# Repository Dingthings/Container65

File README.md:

Simple Arduino Pro-micro based keyboard with QMK support

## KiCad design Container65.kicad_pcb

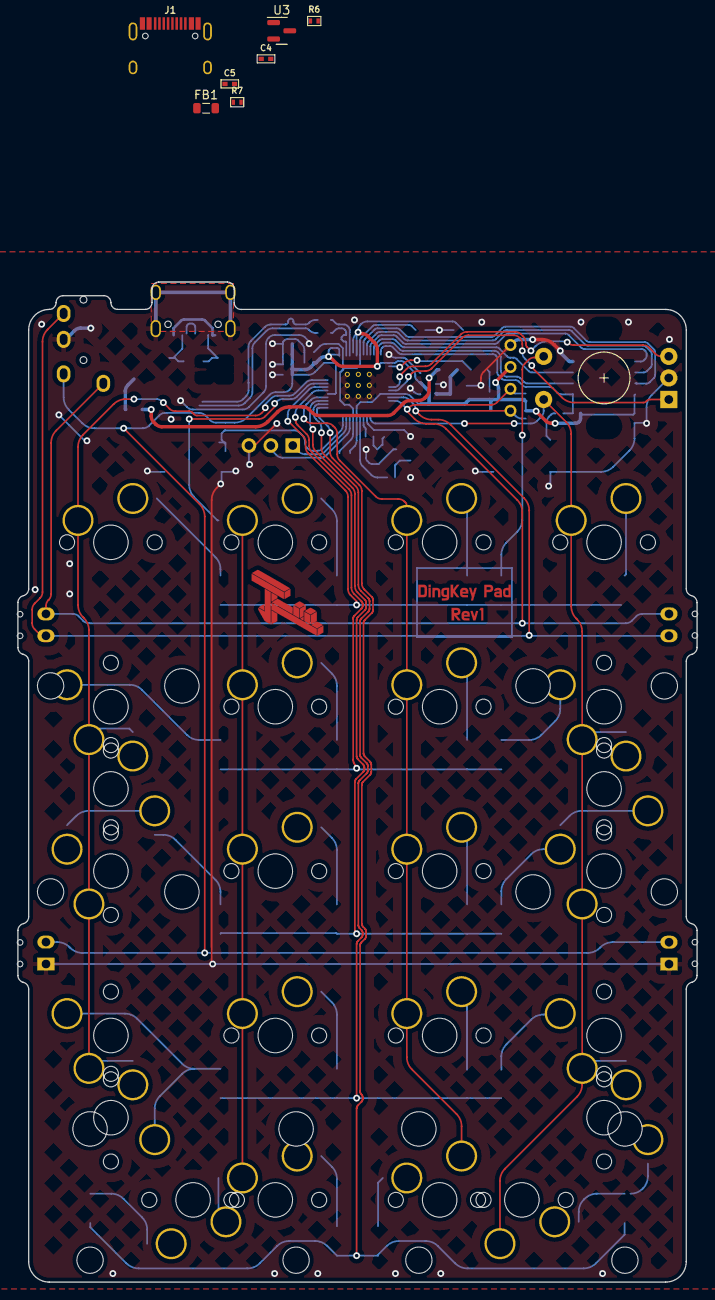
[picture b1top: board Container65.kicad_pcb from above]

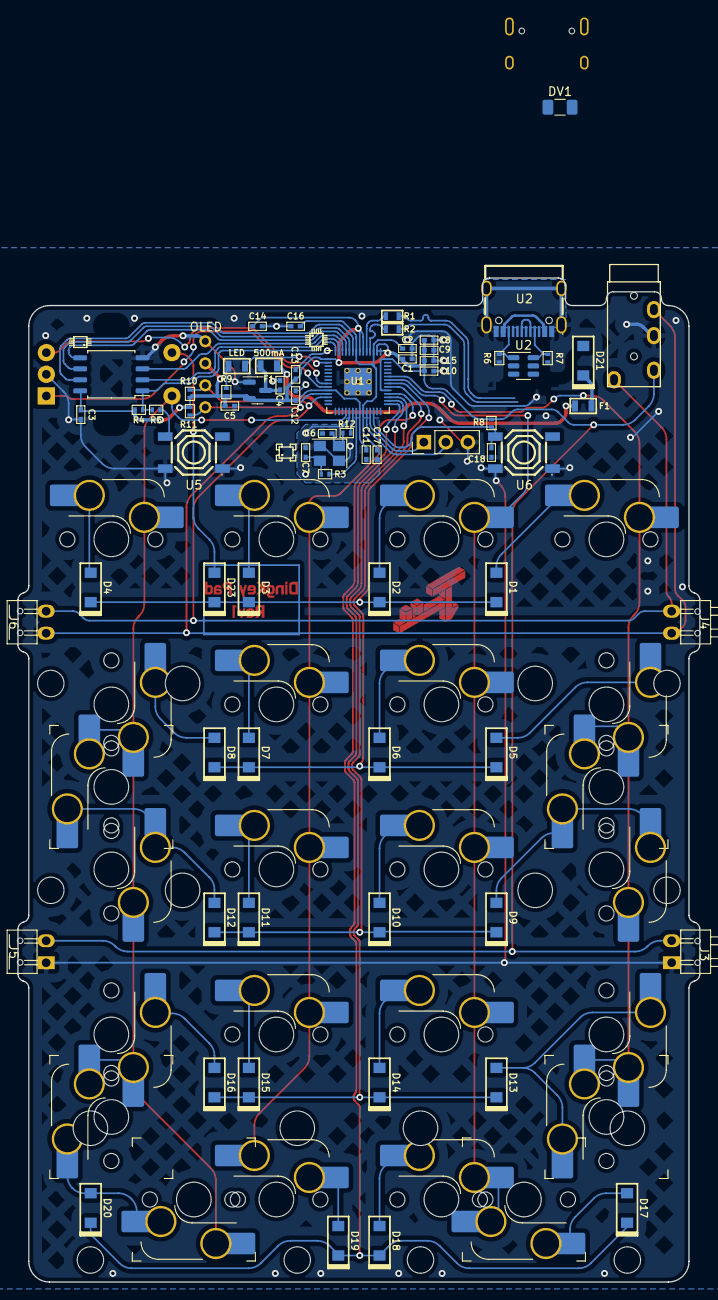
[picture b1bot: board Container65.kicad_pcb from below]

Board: 2 copper layers, 78.7 x 115.9 mm, 107 parts (70 on the bottom side), 63 nets.

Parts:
C1, C2, C4, C4#2, C5, C5#2: 1uF; C_0402
C3, C18: 0.1 uF; C_0402
C6, C7: 30pF; C_0402
C8, C9, C10, C11, C12, C13, C14, C15, C16, C17: 100nF; C_0402
D1, D2, D3, D4, D5, D6, D7, D8, D9, D10, D11, D12, D13, D14, D15, D16, D17, D18, D19, D20, D23: 1N4148W; D_SOD123
D21: Schottky 5819W; D_SOD123
D22: LED; R_0805
DV1: Schottky; Fuse_1206_3216Metric
F1: TLC_PSMD050; Fuse_0805
F1#2: 500mA; Fuse_0805
FB1: (10-50)@100MHz; L_0805_2012Metric
J1: TYPE-C-31-M-12; HRO-TYPE-C-31-M-12-Assembly
J2: Conn_01x03; PinHeader_1x03_P2.54mm_Vertical
J3: POGOm1; 1x02_2.54_Pogo Male GND
J4: POGOm2; 1x02_2.54_Pogo Male
J5: POGOf1; 1x02_2.54_Pogo Female GND
J6: POGOf2; 1x02_2.54_Pogo Female
MX1, MX2, MX3, MX4, MX5, MX6, MX7, MX8, MX9, MX10, MX11, MX12, MX13, MX14, MX15, MX16, MX18, MX19: MX-1U; SW_Hotswap_Kailh_MX_plated_1.00u_Modified
MX17, MX20: MX-2U; SW_Hotswap_Kailh_MX_plated_2.00u_Modified
MX-E-1, MX-E-2, MX-E-3, MX-E-4: MX-2U; SW_Hotswap_Kailh_MX_plated_2.00u_Modified
OL1: OLED; OLED_v2
R1, R2: 27 ohm; R_0603
R3, R5, R12: 1k ohm; R_0402
R4, R8: 10k ohm; R_0402
R6, R6#2, R7, R7#2: 5.1k; R_0402
R9: 1k5 ohm; R_0402
R10, R11: 4.7k; R_0402
SW1: RotaryEncoder_Switch; RotaryEncoder_EC11
U1: RP2040; RP2040-QFN-56
U2: SRV05-4; SOT-23-6
U2#2: TYPE-C-31-M-12; simple-usb-c
U3, U3#2: XC6206PxxxMR; SOT-23
U4: W25Q128JVS; SOIC-8_5.23x5.23mm_P1.27mm
U5: USB Boot; tactile-switch
U6: Reset; tactile-switch
U7: TRRS; TRRS-PJ-320A
X1, X2, X3, X4: 2u Stabilizer; Stabilizer_Cherry_MX_2.00u
Y1: 12MHz - 20pF; Crystal_SMD_3225-4Pin_3.2x2.5mm

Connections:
+1V1: C2.1, C16.1, C17.1, U1.23 (DVDD), U1.45 (VREG_VOUT), U1.50 (DVDD)
+3V3: C1.1, C3.1, C5.1, C5#2.1, C8.1, C9.1, C10.1, C11.1, C12.1, C13.1, C14.1, C15.1, DV1.2 (A), J3.2, J5.2, OL1.3 (VCC), R4.1, R8.2, R9.1, R10.1, R11.1, U1.1 (IOVDD), U1.10 (IOVDD), U1.22 (IOVDD), U1.33 (IOVDD), U1.42 (IOVDD), U1.43 (ADC_AVDD), U1.44 (VREG_IN), U1.48 (USB_VDD), U1.49 (IOVDD), U3.2 (VO), U3#2.2 (VO), U4.8 (VCC), U7.2 (TIP)
+5V: C4#2.1, F1#2.1, U2.5 (VP), U3#2.3 (VI)
CC1: R7.1, R7#2.1, U2.6 (IO4), U2#2.A5 (CC1)
CC2: R6.1, R6#2.1, U2.1 (IO1), U2#2.B5 (CC2)
COL0: MX1.1 (COL), MX5.1 (COL), MX9.1 (COL), MX13.1 (COL), MX-E-1.1 (COL), MX-E-3.1 (COL), U1.37 (GPIO25)
COL1: MX2.1 (COL), MX6.1 (COL), MX10.1 (COL), MX14.1 (COL), MX17.1 (COL), MX18.1 (COL), U1.36 (GPIO24)
COL2: MX3.1 (COL), MX7.1 (COL), MX11.1 (COL), MX15.1 (COL), MX19.2 (ROW), U1.32 (GPIO21)
COL3: MX4.1 (COL), MX8.1 (COL), MX12.1 (COL), MX16.1 (COL), MX20.1 (COL), MX-E-2.1 (COL), MX-E-4.2 (ROW), SW1.S2, U1.18 (GPIO15)
GND: C1.2, C2.2, C3.2, C4.2, C4#2.2, C5.2, C5#2.2, C6.2, C7.2, C8.2, C9.2, C10.2, C11.2, C12.2, C13.2, C14.2, C15.2, C16.2, C17.2, C18.2, J2.3, J3.1, J5.1, OL1.4 (GND), R6.2, R6#2.2, R7.2, R7#2.2, SW1.C, U1.19 (TESTEN), U1.57 (GND), U2.2 (VN), U2#2.0, U2#2.A1 (GND), U2#2.A12 (GND), U2#2.B1 (GND), U2#2.B12 (GND), U3.1 (GND), U3#2.1 (GND), U4.4 (GND), U5.1 (A), U5.2 (B), U6.1 (A), U6.2 (B), U7.3 (RING1), Y1.2, Y1.4
unnamed: C6.1, R12.1, Y1.1
unnamed: D1.2 (A), MX1.2 (ROW)
unnamed: D2.2 (A), MX2.2 (ROW)
unnamed: D3.2 (A), MX3.2 (ROW)
unnamed: D4.2 (A), MX4.2 (ROW)
unnamed: D5.2 (A), MX5.2 (ROW)
unnamed: D6.2 (A), MX6.2 (ROW)
unnamed: D7.2 (A), MX7.2 (ROW)
unnamed: D8.2 (A), MX8.2 (ROW)
unnamed: D9.2 (A), MX9.2 (ROW), MX-E-1.2 (ROW)
unnamed: D10.2 (A), MX10.2 (ROW)
unnamed: D11.2 (A), MX11.2 (ROW)
unnamed: D12.2 (A), MX12.2 (ROW), MX-E-2.2 (ROW)
unnamed: D13.2 (A), MX13.2 (ROW), MX-E-3.2 (ROW)
unnamed: D14.2 (A), MX14.2 (ROW)
unnamed: D15.2 (A), MX15.2 (ROW)
unnamed: D16.2 (A), MX16.2 (ROW)
unnamed: D17.2 (A), MX17.2 (ROW)
unnamed: D18.2 (A), MX18.2 (ROW)
unnamed: D19.2 (A), MX19.1 (COL)
unnamed: D20.2 (A), MX20.2 (ROW), MX-E-4.1 (COL)
unnamed: D21.1 (K), F1.1
unnamed: D22.2 (A), R9.2
unnamed: D23.2 (A), SW1.S1
unnamed: C4.1, DV1.1 (K), F1.2, F1#2.2, U3.3 (VI)
unnamed: R5.2, U5.3 (C), U5.4 (D)
OSC_IN: C7.1, R3.1, Y1.3
OSC_OUT: R12.2, U1.20 (XIN)
QSPI_SCLK: U1.52 (QSPI_SCLK), U4.6 (CLK)
QSPI_SD0: U1.53 (QSPI_SD0), U4.5 (DI(IO0))
QSPI_SD1: U1.55 (QSPI_SD1), U4.2 (DO(IO1))
QSPI_SD2: U1.54 (QSPI_SD2), U4.3 (IO2)
QSPI_SD3: U1.51 (QSPI_SD3), U4.7 (IO3)
QSPI_SS: R4.2, R5.1, U1.56 (QSPI_SS), U4.1 (~CS)
ROW0: D1.1 (K), D2.1 (K), D3.1 (K), D4.1 (K), D23.1 (K), U1.35 (GPIO23)
ROW1: D5.1 (K), D6.1 (K), D7.1 (K), D8.1 (K), U1.34 (GPIO22)
ROW2: D9.1 (K), D10.1 (K), D11.1 (K), D12.1 (K), U1.31 (GPIO20)
ROW3: D13.1 (K), D14.1 (K), D15.1 (K), D16.1 (K), U1.30 (GPIO19)
ROW4: D17.1 (K), D18.1 (K), D19.1 (K), D20.1 (K), U1.29 (GPIO18)
RUN: C18.1, R8.1, U1.26 (RUN), U6.3 (C), U6.4 (D)
SCL: J4.2, J6.2, OL1.2 (SCL), R10.2, U1.12 (GPIO9), U7.1 (SLEEVE)
SDA: J4.1, J6.1, OL1.1 (SDA), R11.2, U1.11 (GPIO8), U7.4 (RING2)
SWCLK: J2.2, U1.24 (SWCLK)
SWD: J2.1, U1.25 (SWD)
USB+: R1.2, U2.3 (IO2), U2#2.A6 (DP1), U2#2.B6 (DP2)
USB-: R2.2, U2.4 (IO3), U2#2.A7 (DN1), U2#2.B7 (DN2)
USB_MCU+: R1.1, U1.47 (USB_DP)
USB_MCU-: R2.1, U1.46 (USB_DM)
USER_LED: D22.1 (K), U1.2 (GPIO0)
VBUS: D21.2 (A), FB1.1, U2#2.A4 (VBUS), U2#2.A9 (VBUS), U2#2.B4 (VBUS), U2#2.B9 (VBUS)
XOUT_MCU: R3.2, U1.21 (XOUT)
encA: SW1.B, U1.8 (GPIO6)
encB: SW1.A, U1.9 (GPIO7)

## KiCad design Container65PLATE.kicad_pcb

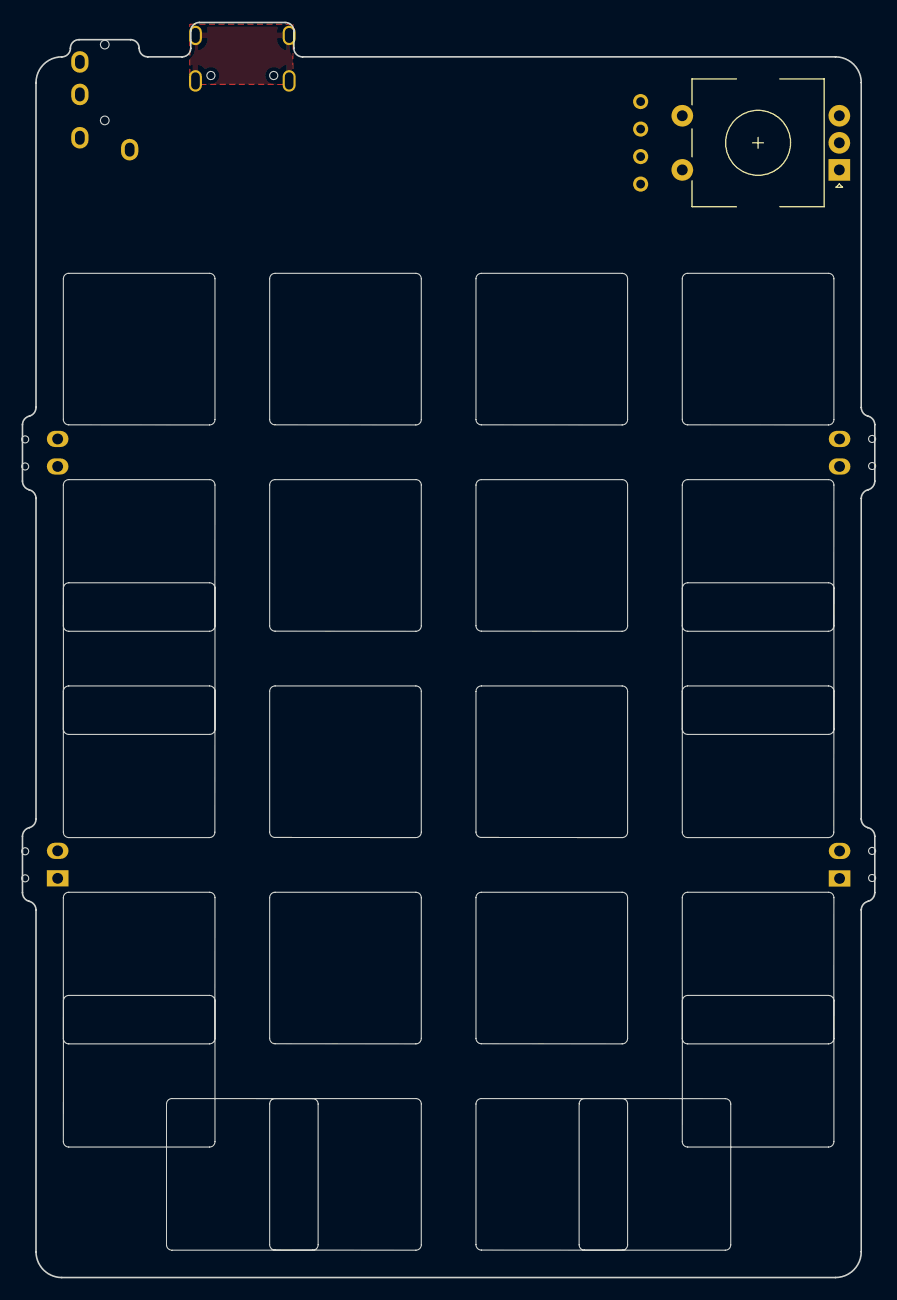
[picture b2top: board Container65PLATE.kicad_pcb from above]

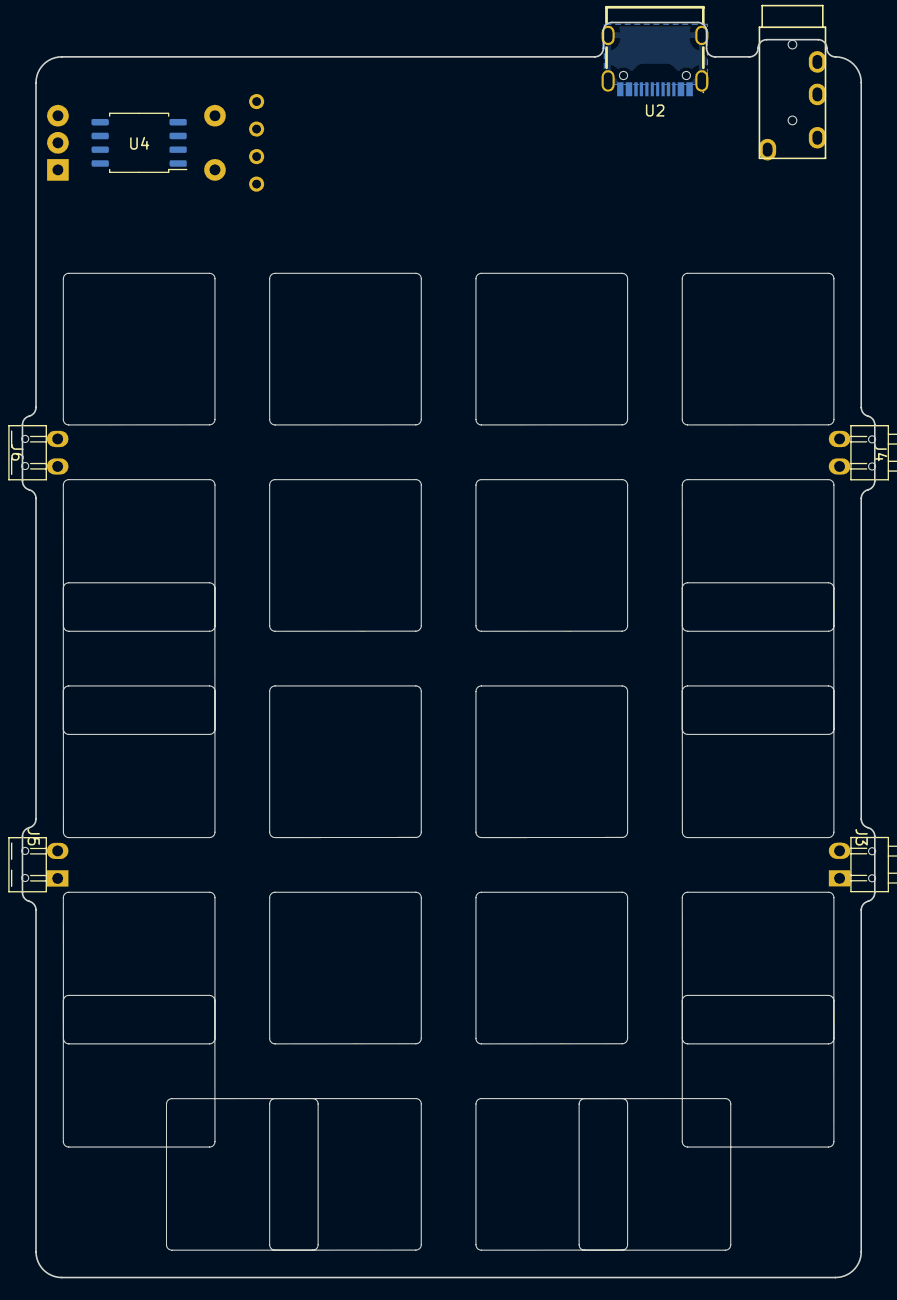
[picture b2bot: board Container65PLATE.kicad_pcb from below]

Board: 2 copper layers, 78.7 x 115.9 mm, 37 parts (7 on the bottom side), 7 nets, no tracks yet.

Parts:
J3: POGOm1; 1x02_2.54_Pogo Male GND
J4: POGOm2; 1x02_2.54_Pogo Male
J5: POGOf1; 1x02_2.54_Pogo Female GND
J6: POGOf2; 1x02_2.54_Pogo Female
MX1, MX2, MX3, MX4, MX5, MX6, MX7, MX8, MX9, MX10, MX11, MX12, MX13, MX14, MX15, MX16, MX18, MX19: MX-1U; MX100
MX17, MX20: MX-2U; MX100
MX-E-1, MX-E-2, MX-E-3, MX-E-4: MX-2U; MX100
OL1: OLED; OLED_v2
SW1: RotaryEncoder_Switch; RotaryEncoder_EC11
U2: TYPE-C-31-M-12; simple-usb-c
U4: W25Q128JVS; SOIC-8_5.23x5.23mm_P1.27mm
U7: TRRS; TRRS-PJ-320A
X1, X2, X3, X4: 2u Stabilizer; MX_Stabilizer_Cutout-2u

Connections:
+3V3: J3.2, J5.2, OL1.3 (VCC), U4.8 (VCC), U7.2 (TIP)
GND: J3.1, J5.1, OL1.4 (GND), SW1.C, U2.0, U2.A1 (GND), U2.A12 (GND), U2.B1 (GND), U2.B12 (GND), U4.4 (GND), U7.3 (RING1)
SCL: J4.2, J6.2, OL1.2 (SCL), U7.1 (SLEEVE)
SDA: J4.1, J6.1, OL1.1 (SDA), U7.4 (RING2)
USB+: U2.A6 (DP1), U2.B6 (DP2)
USB-: U2.A7 (DN1), U2.B7 (DN2)
VBUS: U2.A4 (VBUS), U2.A9 (VBUS), U2.B4 (VBUS), U2.B9 (VBUS)

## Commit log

2022-09-05 Project created
    Generate files
2022-09-05 Add submodules
2022-09-05 Add libraries
2022-09-05 MCU Schematic
2022-09-13 Add keebio
2022-09-13 Add USB C
2022-09-19 Matrix created
2022-09-26 Design
2022-09-26 Plate footprints
2022-10-02 Copy from backup
2022-10-07 Board edits
2022-10-07 Added OLED
2022-10-08 Removed 1u
2022-10-09 Finished routing MCU
2022-10-09 Finished routing
2022-10-12 More routing fix
2022-10-29 Add eblaster lib
